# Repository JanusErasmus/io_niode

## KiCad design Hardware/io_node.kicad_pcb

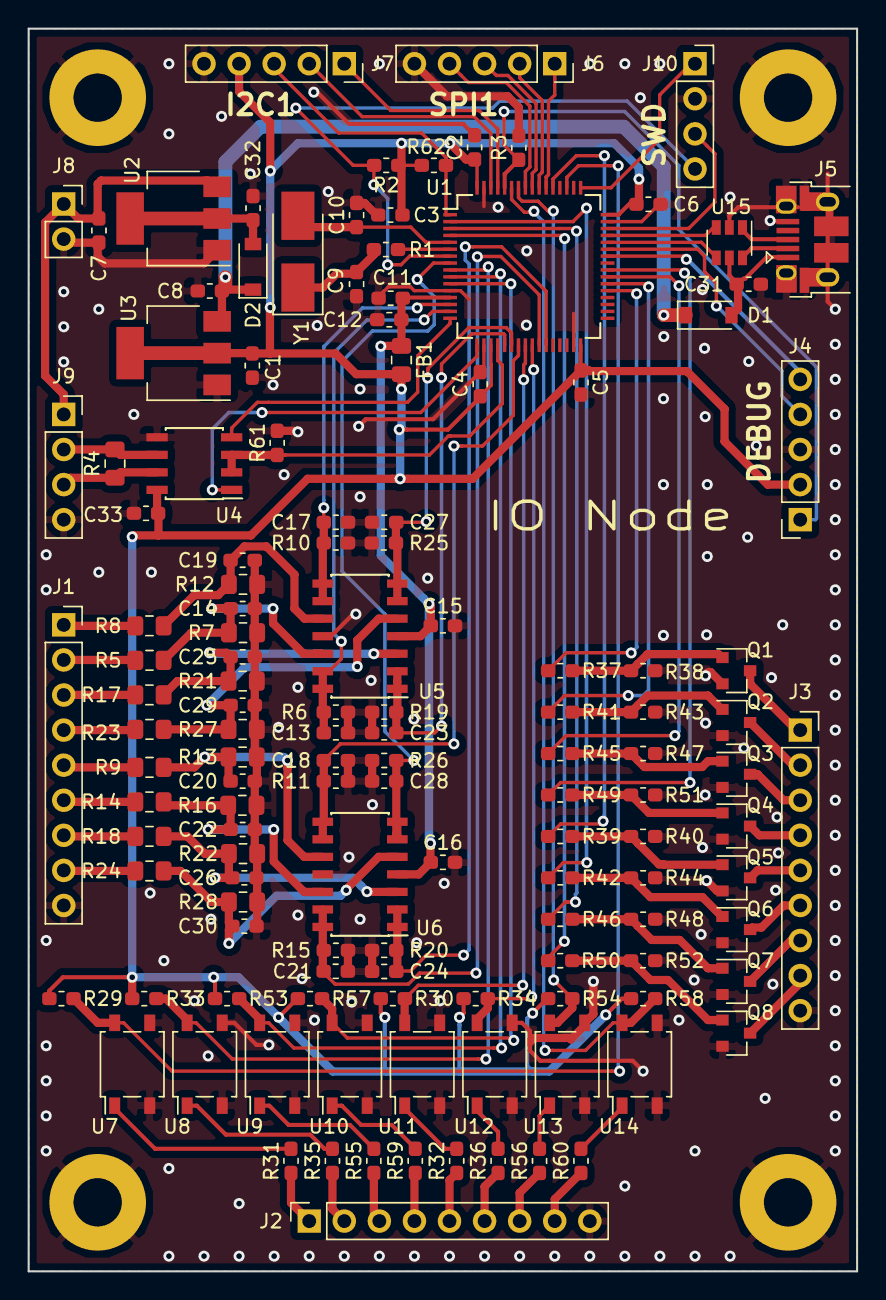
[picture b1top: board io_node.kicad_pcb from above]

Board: 2 copper layers, 60.0 x 90.0 mm, 136 parts (0 on the bottom side), 104 nets.

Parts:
C1, C7: 4_7UF; C_0603_1608Metric_Pad1.05x0.95mm_HandSolder
C2, C3, C4, C5, C6, C8, C11, C14, C15, C16, C19, C20, C22, C25, C26, C29, C30, C31, C32, C33: 100NF; C_0603_1608Metric_Pad1.05x0.95mm_HandSolder
C9, C10: 33PF; C_0603_1608Metric_Pad1.05x0.95mm_HandSolder
C12, C13, C17, C18, C21, C23, C24, C27, C28: 1NF; C_0603_1608Metric_Pad1.05x0.95mm_HandSolder
D1, D2: B5819W; D_SOD-123
FB1: 600R; R_0805_2012Metric_Pad1.15x1.40mm_HandSolder
H1, H2, H3, H4: MountingHole_Pad; MountingHole_3.5mm_Pad
J1, J2, J3: Conn_01x09; PinSocket_1x09_P2.54mm_Vertical
J4, J6, J7: Conn_01x05; PinSocket_1x05_P2.54mm_Vertical
J5: USB_B_Micro; USB_Micro-B_Amphenol_10103594-0001LF_Horizontal
J8: Conn_01x02; PinSocket_1x02_P2.54mm_Vertical
J9, J10: Conn_01x04; PinSocket_1x04_P2.54mm_Vertical
Q1, Q2, Q3, Q4, Q5, Q6, Q7, Q8: 2N7002; SOT-23
R1, R31, R32, R35, R36, R55, R56, R59, R60: 470R; R_0603_1608Metric_Pad1.05x0.95mm_HandSolder
R2, R3, R6, R10, R11, R15, R19, R20, R25, R26, R29, R30, R33, R34, R38, R40, R43, R44, R47, R48, R51, R52, R53, R54, R57, R58, R61: 10K; R_0603_1608Metric_Pad1.05x0.95mm_HandSolder
R4: 120R; R_0805_2012Metric_Pad1.15x1.40mm_HandSolder
R5, R7, R8, R9, R12, R13, R14, R16, R17, R18, R21, R22, R23, R24, R27, R28: 10K; R_0805_2012Metric_Pad1.15x1.40mm_HandSolder
R37, R39, R41, R42, R45, R46, R49, R50: 1K; R_0603_1608Metric_Pad1.05x0.95mm_HandSolder
R62: 0R; R_0603_1608Metric_Pad1.05x0.95mm_HandSolder
U1: STM32F103RBT6; LQFP-64_10x10mm_P0.5mm
U2: AMS1117-5.0; SOT-223-3_TabPin2
U3: AMS1117-3.3; SOT-223-3_TabPin2
U4: SP3485EN; SOIC-8_3.9x4.9mm_P1.27mm
U5, U6: LM324DT; SOIC-14_3.9x8.7mm_P1.27mm
U7, U8, U9, U10, U11, U12, U13, U14: EL357N-G; SO-4_4.4x4.3mm_P2.54mm
U15: USBLC6-2SC6; SOT-23-6
Y1: 8 MHz; Crystal_SMD_5032-2Pin_5.0x3.2mm_HandSoldering

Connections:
+3.3VA: C11.1, C12.1, C15.1, C16.1, FB1.1, U1.13, U5.4, U6.4
+3V3: C1.1, C2.1, C3.1, C4.1, C5.1, C6.1, C33.1, FB1.2, J4.2, J7.4, R2.1, R29.1, R30.1, R33.1, R34.1, R53.1, R54.1, R57.1, R58.1, R62.2, U1.19, U1.32, U1.48, U1.64, U3.2, U4.8
+5V: C8.1, D1.1, D2.1, U3.3
+12V: C7.1, J8.1, J9.1, U2.3
+BATT: J7.3, R62.1, U1.1
/ADC_IN0: C17.1, R10.1, U1.14, U5.8, U5.9
/ADC_IN1: C13.1, R6.1, U1.15, U5.13, U5.14
/ADC_IN5: C23.1, R19.1, U1.21, U5.1, U5.2
/ADC_IN6: C27.1, R25.1, U1.22, U5.6, U5.7
/ADC_IN7: C18.1, R11.1, U1.23, U6.8, U6.9
/ADC_IN8: C21.1, R15.1, U1.26, U6.13, U6.14
/ADC_IN9: C24.1, R20.1, U1.27, U6.1, U6.2
/ADC_IN10: C28.1, R26.1, U1.8, U6.6, U6.7
/Analog/AIN_0: J1.1, R8.1
/Analog/AIN_1: J1.2, R5.1
/Analog/AIN_2: J1.3, R17.1
/Analog/AIN_3: J1.4, R23.1
/Analog/AIN_4: J1.5, R9.1
/Analog/AIN_5: J1.6, R14.1
/Analog/AIN_6: J1.7, R18.1
/Analog/AIN_7: J1.8, R24.1
/BOOT0: J4.1, R3.1, U1.60
/I2C1_SCL: J7.1, U1.61
/I2C1_SDA: J7.2, U1.62
/IN_0: R29.2, U1.51, U7.4
/IN_1: R33.2, U1.9, U8.4
/IN_2: R53.2, U1.10, U9.4
/IN_3: R57.2, U1.11, U10.4
/IN_4: R30.2, U1.24, U11.4
/IN_5: R34.2, U1.25, U12.4
/IN_6: R54.2, U1.58, U13.4
/IN_7: R58.2, U1.59, U14.4
/Input/DIN_0: J2.1, R31.1
/Input/DIN_1: J2.2, R35.1
/Input/DIN_2: J2.3, R55.1
/Input/DIN_3: J2.4, R59.1
/Input/DIN_4: J2.5, R32.1
/Input/DIN_5: J2.6, R36.1
/Input/DIN_6: J2.7, R56.1
/Input/DIN_7: J2.8, R60.1
/NRST: J10.4, R2.2, U1.7
/OUT_4: R39.1, U1.53
/OUT_5: R42.1, U1.2
/OUT_6: R46.1, U1.3
/OUT_7: R50.1, U1.4
/Output/DOT_0: J3.1, Q1.3
/Output/DOT_1: J3.2, Q2.3
/Output/DOT_2: J3.3, Q3.3
/Output/DOT_3: J3.4, Q4.3
/Output/DOT_4: J3.5, Q5.3
/Output/DOT_5: J3.6, Q6.3
/Output/DOT_6: J3.7, Q7.3
/Output/DOT_7: J3.8, Q8.3
/RS485_A: J9.2, R4.2, U4.6
/RS485_B: J9.3, R4.1, U4.7
/SPI1_CS: J6.1, U1.54
/SPI1_MISO: J6.3, U1.56
/SPI1_MOSI: J6.4, U1.57
/SPI1_SCK: J6.2, U1.55
/SWCLK: J10.1, U1.49
/SWDIO: J10.3, U1.46
/TIM3_CH1: R37.1, U1.37
/TIM3_CH2: R41.1, U1.38
/TIM3_CH3: R45.1, U1.39
/TIM3_CH4: R49.1, U1.40
/USART1_RX: J4.4, U1.43
/USART1_TX: J4.5, U1.42
/USART2_DE: R61.1, U1.20, U4.2, U4.3
/USART2_RX: U1.17, U4.1
/USART2_TX: U1.16, U4.4
/USB_CONN_DM: J5.2, U15.6
/USB_CONN_DP: J5.3, U15.1
/USB_N: U1.44, U15.4
/USB_P: U1.45, U15.3
GND: C1.2, C2.2, C3.2, C4.2, C5.2, C6.2, C7.2, C8.2, C9.2, C10.2, C11.2, C12.2, C13.2, C14.2, C15.2, C16.2, C17.2, C18.2, C19.2, C20.2, C21.2, C22.2, C23.2, C24.2, C25.2, C26.2, C27.2, C28.2, C29.2, C30.2, C31.2, C32.2, C33.2, H1.1, H2.1, H3.1, H4.1, J1.9, J2.9, J3.9, J4.3, J5.5, J5.6, J6.5, J7.5, J8.2, J9.4, J10.2, Q1.2, Q2.2, Q3.2, Q4.2, Q5.2, Q6.2, Q7.2, Q8.2, R3.2, R6.2, R7.2, R10.2, R11.2, R12.2, R13.2, R15.2, R16.2, R19.2, R20.2, R21.2, R22.2, R25.2, R26.2, R27.2, R28.2, R38.2, R40.2, R43.2, R44.2, R47.2, R48.2, R51.2, R52.2, R61.2, U1.12, U1.18, U1.31, U1.47, U1.63, U2.1, U3.1, U4.5, U5.11, U6.11, U7.2, U7.3, U8.2, U8.3, U9.2, U9.3, U10.2, U10.3, U11.2, U11.3, U12.2, U12.3, U13.2, U13.3, U14.2, U14.3, U15.2
unnamed: C9.1, R1.2, Y1.1
unnamed: C10.1, U1.5, Y1.2
unnamed: C14.1, R5.2, R7.1, U5.12
unnamed: C19.1, R8.2, R12.1, U5.10
unnamed: C20.1, R9.2, R13.1, U6.10
unnamed: C22.1, R14.2, R16.1, U6.12
unnamed: C25.1, R17.2, R21.1, U5.3
unnamed: C26.1, R18.2, R22.1, U6.3
unnamed: C29.1, R23.2, R27.1, U5.5
unnamed: C30.1, R24.2, R28.1, U6.5
unnamed: C32.1, D2.2, U2.2
unnamed: Q1.1, R37.2, R38.1
unnamed: Q2.1, R41.2, R43.1
unnamed: Q3.1, R45.2, R47.1
unnamed: Q4.1, R49.2, R51.1
unnamed: Q5.1, R39.2, R40.1
unnamed: Q6.1, R42.2, R44.1
unnamed: Q7.1, R46.2, R48.1
unnamed: Q8.1, R50.2, R52.1
unnamed: R1.1, U1.6
unnamed: R31.2, U7.1
unnamed: R32.2, U11.1
unnamed: R35.2, U8.1
unnamed: R36.2, U12.1
unnamed: R55.2, U9.1
unnamed: R56.2, U13.1
unnamed: R59.2, U10.1
unnamed: R60.2, U14.1
VBUS: C31.1, D1.2, J5.1, U15.5

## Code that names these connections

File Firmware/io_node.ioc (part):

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Mcu.Name=STM32F103R(8-B)Tx
Mcu.Package=LQFP64
Mcu.UserName=STM32F103RBTx
PA0-WKUP.Signal=ADCx_IN0
PA1.Signal=ADCx_IN1
PA10.Mode=Asynchronous
PA10.Signal=USART1_RX
PA13.GPIOParameters=GPIO_Label
PA13.GPIO_Label=NRF_CE
PA13.Signal=GPIO_Output
PA14.GPIOParameters=GPIO_Label
PA14.GPIO_Label=NRF_IRQ
PA14.Signal=GPIO_Input
PA2.Mode=Asynchronous
PA2.Signal=USART2_TX
PA3.Mode=Asynchronous
PA3.Signal=USART2_RX
PA4.GPIOParameters=GPIO_Label
PA4.GPIO_Label=USART2_DE
PA4.Signal=GPIO_Output
PA5.Signal=ADCx_IN5
PA6.Signal=ADCx_IN6
PA7.Signal=ADCx_IN7
PA9.Mode=Asynchronous
PA9.Signal=USART1_TX
PB0.Signal=ADCx_IN8
PB1.Signal=ADCx_IN9
PB3.Mode=Full_Duplex_Master
PB3.Signal=SPI1_SCK
PB4.Mode=Full_Duplex_Master
PB4.Signal=SPI1_MISO
PB5.Mode=Full_Duplex_Master
PB5.Signal=SPI1_MOSI
PB6.GPIOParameters=GPIO_Label
PB6.GPIO_Label=IN_6
PB6.Signal=GPIO_Input
PB7.GPIOParameters=GPIO_Label
PB7.GPIO_Label=IN_7
PB7.Signal=GPIO_Input
PB8.Mode=I2C
PB8.Signal=I2C1_SCL
PB9.Mode=I2C
PB9.Signal=I2C1_SDA
PC0.Signal=ADCx_IN10
PC1.GPIOParameters=GPIO_Label
PC1.GPIO_Label=IN_1
PC1.Signal=GPIO_Input
PC10.GPIOParameters=GPIO_Label
PC10.GPIO_Label=IN_0
PC10.Signal=GPIO_Input
PC12.GPIOParameters=GPIO_Label
PC12.GPIO_Label=OUT_4
PC12.Signal=GPIO_Output
PC13-TAMPER-RTC.GPIOParameters=GPIO_Label
PC13-TAMPER-RTC.GPIO_Label=OUT_5
PC13-TAMPER-RTC.Signal=GPIO_Output
PC14-OSC32_IN.GPIOParameters=GPIO_Label
PC14-OSC32_IN.GPIO_Label=OUT_6
PC14-OSC32_IN.Signal=GPIO_Output
PC15-OSC32_OUT.GPIOParameters=GPIO_Label
PC15-OSC32_OUT.GPIO_Label=OUT_7
PC15-OSC32_OUT.Signal=GPIO_Output
PC2.GPIOParameters=GPIO_Label
PC2.GPIO_Label=IN_2
PC2.Signal=GPIO_Input
PC3.GPIOParameters=GPIO_Label
PC3.GPIO_Label=IN_3
PC3.Signal=GPIO_Input
PC4.GPIOParameters=GPIO_Label
PC4.GPIO_Label=IN_4
PC4.Signal=GPIO_Input
PC5.GPIOParameters=GPIO_Label
PC5.GPIO_Label=IN_5
PC5.Signal=GPIO_Input
PC6.GPIOParameters=GPIO_Label
PC6.GPIO_Label=OUT_0
PC6.Signal=GPIO_Output
PC7.GPIOParameters=GPIO_Label
PC7.GPIO_Label=OUT_1
PC7.Signal=GPIO_Output
PC8.GPIOParameters=GPIO_Label
PC8.GPIO_Label=OUT_2
PC8.Signal=GPIO_Output
PC9.GPIOParameters=GPIO_Label
PC9.GPIO_Label=OUT_3
PC9.Signal=GPIO_Output
PD0-OSC_IN.Mode=HSE-External-Oscillator
PD0-OSC_IN.Signal=RCC_OSC_IN
PD1-OSC_OUT.Mode=HSE-External-Oscillator
PD1-OSC_OUT.Signal=RCC_OSC_OUT
PD2.GPIOParameters=GPIO_Label
PD2.GPIO_Label=SPI1_CS
PD2.Signal=GPIO_Output
RCC.SYSCLKFreq_VALUE=72000000
RCC.SYSCLKSource=RCC_SYSCLKSOURCE_PLLCLK
board=custom

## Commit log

2020-10-01 inital commit
2020-10-12 Add in and output drivers
2020-10-12 Add USB protection
2020-10-14 Add power connector
2020-10-15 Layout DIN DOT
2020-10-16 Add SWD
2020-10-16 Update USB footprint
2020-10-18 Adjust BOM for Node with divider
2020-10-18 OP-AMP power was incorrect
2020-10-18 RS485 TX and RX was incorrect
2020-10-18 Debug RX TX swapped
2020-10-18 Add Vbat
2020-10-28 Add example firmware
2020-10-30 Add ADC sampling
2020-10-30 Disable USB, fix USB protection
2020-10-31 Add NRF driver
2020-10-31 ADD SSD1306 display on I2C
2020-12-25 Let Cube HAL handle other interrupts from UART
2020-12-31 CLI have a history of 16 commands
2021-01-13 Add enclosure design
2021-01-16 Add DS18B20 temperature sensor [bit bang, DWT(Data watchpoint trigger) us delay]
2021-01-17 Clean main, sample DS18B20 and send with V[0]
